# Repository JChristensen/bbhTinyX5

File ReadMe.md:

# ATtinyX5 Breadboard Helper #
http://github.com/JChristensen/bbhTinyX5  
ReadMe file  
Jack Christensen Jan 2015  

## Introduction ##

ATtiny Breadboard Helpers are the easiest way to breadboard Atmel ATtiny24/44/84 and ATtiny25/45/85 micrcontrollers! These small boards contain everything needed to run an ATtiny microcontroller, including:
- ICSP header
- Filter and bypass capacitors
- Reset button with pullup resistor
- LED with current-limiting resistor

The Breadboard Helper breaks out all the MCU's pins to a header and also connects to the breadboard's power rails. Plug the Breadboard Helper into a breadboard, add power, connect a programmer, and the microcontroller is ready to go!

PC boards can be ordered [from OSH Park](https://oshpark.com/shared_projects/kbM0Jfiz).  
A Bill of Materials with Mouser part numbers is part of this repo.  
See the ATtinyX4 Breadboard Helper [here](https://github.com/JChristensen/bbhTinyX4).

## Power Connection (see photos below)##

A two-pin header connects the Breadboard Helper to the breadboard's power rails. This header should be soldered ***either*** into the position labeled **"a"** ***or*** into the position labeled **"b"**.

Use position **"a"** for breadboards where the power rail holes line up with those in the main part of the breadboard (most full-size breadboards). Use position **"b"** for breadboards where the power rail holes are staggered between those in the main part of the breadboard (most half-size breadboards).

Observe polarity carefully and ***do not*** solder headers into both positions **"a"** and **"b"**, as the result will likely not fit into any breadboard!

## Arduino Pin Mapping ##

The 6-pin header is labeled with Arduino pin numbers 0-4 plus RESET, using the pin mapping from the [Arduino-Tiny core](https://code.google.com/p/arduino-tiny/). Other cores may be used with the Breadboard Helper but be aware that the pin mapping may be different. The AVR port and pin numbers are also labeled for easy reference.

The LED is connected to Arduino pin 2 or PB2 (SCK/USCK/SCL/ADC1/T0/INT0/PCINT2).

## Make the right power connection ##

Some breadboards have holes in the power rails that line up with those in the main part of the breadboard -- this is **Type "a"**.  

Some breadboards have holes in the power rails that are staggered between those in the main part of the breadboard -- this is **Type "b"**.  

Solder the two-pin power rail header into position **"a"** *or* position **"b"**, *NOT BOTH!*

Add power (observe polarity!), connect a programmer and the ATtiny is ready to go!

## CC BY-SA ##
"ATtinyX5 Breadboard Helper" by Jack Christensen is licensed under [CC BY-SA 4.0](http://creativecommons.org/licenses/by-sa/4.0/).

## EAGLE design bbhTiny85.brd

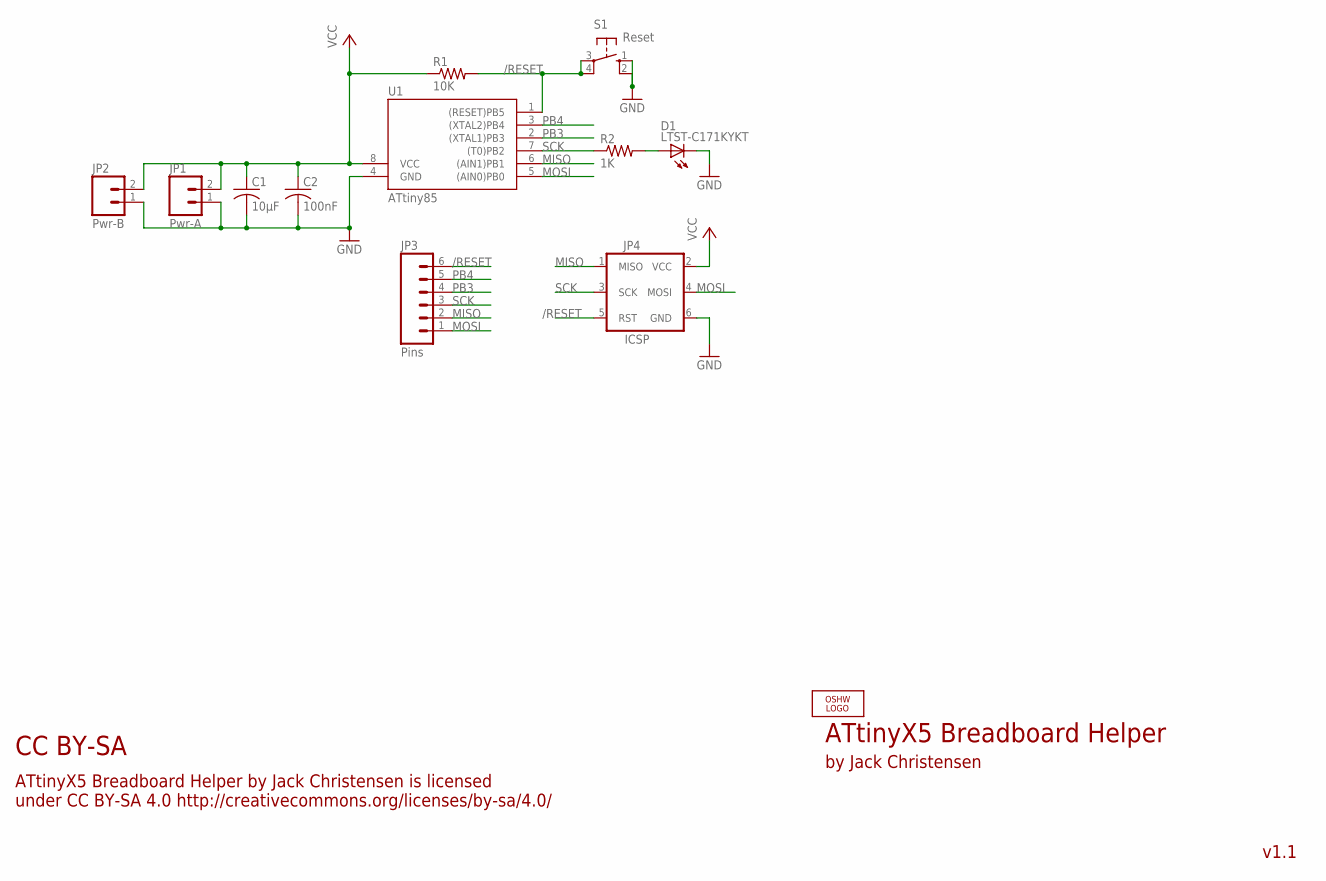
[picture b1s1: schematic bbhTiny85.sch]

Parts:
C1: 10µF; M0805
C2: 100nF; M0805
D1: LTST-C171KYKT; D0805A
JP1: Pwr-A; 1X02
JP2: Pwr-B; 1X02
JP3: Pins; 1X06
JP4: ICSP; 2X3_LOCK
LOGO1: OSHW_LOGO_8MILX0100-NT; OSHW_8X100_NOTEXT
R1: 10K; M0805
R2: 1K; M0805
S1: Reset; B3F-10XXOCT
U1: ATtiny85; DIL08

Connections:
/RESET: JP3.6, JP4.5 (RST), R1.2, S1.3, S1.4 (P1), U1.1 ((RESET)PB5)
GND: C1.2, C2.2, D1.K (C), JP1.1, JP2.1, JP4.6 (GND), S1.1 (S), S1.2 (S1), U1.4 (GND)
MISO: JP3.2, JP4.1 (MISO), U1.6 ((AIN1)PB1)
MOSI: JP3.1, JP4.4 (MOSI), U1.5 ((AIN0)PB0)
unnamed: D1.A, R2.2
PB3: JP3.4, U1.2 ((XTAL1)PB3)
PB4: JP3.5, U1.3 ((XTAL2)PB4)
SCK: JP3.3, JP4.3 (SCK), R2.1, U1.7 ((T0)PB2)
VCC: C1.1, C2.1, JP1.2, JP2.2, JP4.2 (VCC), R1.1, U1.8 (VCC)

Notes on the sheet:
ATtinyX5 Breadboard Helper
by Jack Christensen
ATtinyX5 Breadboard Helper by Jack Christensen is licensed under CC BY-SA 4.0 http://creativecommons.org/licenses/by-sa/4.0/
CC BY-SA
v1.1

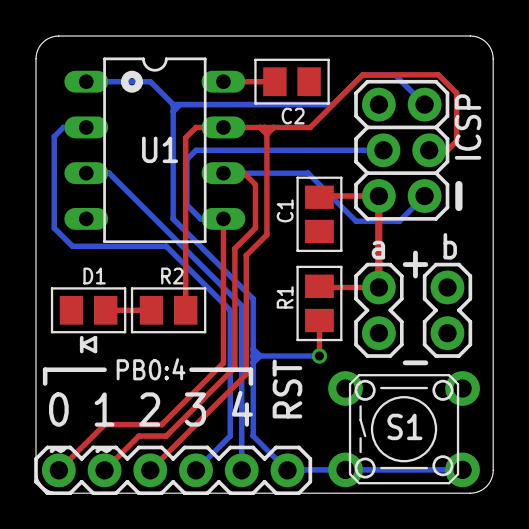
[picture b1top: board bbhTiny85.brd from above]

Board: 2 copper layers, 25.4 x 25.4 mm, 12 parts (1 on the bottom side), 9 nets.

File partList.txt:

Partlist

Exported from bbhTiny85.sch at 12/17/2014 6:19:00 PM

EAGLE Version 6.4.0 Copyright (c) 1988-2013 CadSoft

Assembly variant: 

Part     Value          Device                Package     Library  Sheet

C1       10µF           C-USM0805             M0805       _jc      1
C2       100nF          C-USM0805             M0805       _jc      1
D1       Yellow         LEDD0805A             D0805A      _jc      1
JP1      Pwr-A          M02PTH                1X02        SparkFun 1
JP2      Pwr-B          M02PTH                1X02        SparkFun 1
JP3      Pins           M06SIP                1X06        SparkFun 1
JP4      ICSP           AVR_SPI_PRG_62X3_LOCK 2X3_LOCK    _jc      1
R1       10K            R-US_M0805            M0805       _jc      1
R2       1K             R-US_M0805            M0805       _jc      1
S1       Reset          10-XXOCT              B3F-10XXOCT _jc      1
U1       ATtiny85       TINY10P               DIL08       atmel    1

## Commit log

2015-01-07 Initial commit (v1.1). Minor silkscreen change from v1.
2015-01-16 Add images, update ReadMe, etc.
2015-01-16 Update ReadMe.
2015-01-16 Fix link in ReadMe.

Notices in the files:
parts and their libraries:
SparkFun: Licensing: CC v3.0 Share-Alike You are welcome to use this library for commercial purposes.
